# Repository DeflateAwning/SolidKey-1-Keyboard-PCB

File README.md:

# SolidKey-1-Keyboard-PCB
A capacitive touch QMK keyboard, with aspirations of replacing the Framework 13 keyboard

## Inspiration

* This project is inspired by [ebastler's UnMechanical Keyboard](https://github.com/ebastler/UnMechanical).

## Goals

* Make a columnar keyboard with a capacitive touch interface.
* Make the keyboard fit between the Framework 13 keyboard space and screen. Be compatible with the Framework 13 input cover's wiring.
* Base the locations of the keys on the Iris 6 keyboard.
* Parts:
    * RP2040 microcontroller
    * USB-C
    * Vibration motor
    * No LEDs!
* Low-ish power, low mass
* <$80 for a fully-assembled keyboard from JLCPCB

## Licence

The hardware component of this project is licenced under the `CERN Open Hardware Licence Version 2 - Weakly Reciprocal` licence. Variations must be shared under the same licence (or equivalent) licence. Commercial use is allowed, but the source must be shared, and it must be released/sold under a different name.

## Notes

* Framework 13 keyboard dimensions: 276.76mm x 105.0mm x 1.74mm, at the bottom of the taper up, based on their full STEP CAD model.
* For the 276mm x 105mm PCB from JLCPCB, it costs:
    * US$16.80 for 0.6mm thick, LeadFree HASL
    * US$60.60 for 0.4mm thick, requiring ENIG
    * US$10 shipping for these thin boards.
    * US$50 for 0.6mm assembly ("Standard"), but US$26 for 0.8mm assembly ("Economic").
    * 0.8mm weighs 54g each. 0.6mm weighs 40g-54g each.

## Resources

* RP2040 Design Guide: https://datasheets.raspberrypi.com/rp2040/hardware-design-with-rp2040.pdf
* CY8CMBR3116 Capacitive Touch Guides:
    * Datasheet: https://www.infineon.com/cms/en/product/microcontroller/sensing-controller/capsense-controllers/capsense-mbr3/cy8cmbr3116-lqxit/
    * CY8CMBR3xxx CapSense Design Guide: https://www.cypress.com/?rID=90800
    * Getting Started with CapSense: https://www.cypress.com/?rID=48787

## Future Work

* Add a dot mouse thing, like the ThinkPad keyboards.

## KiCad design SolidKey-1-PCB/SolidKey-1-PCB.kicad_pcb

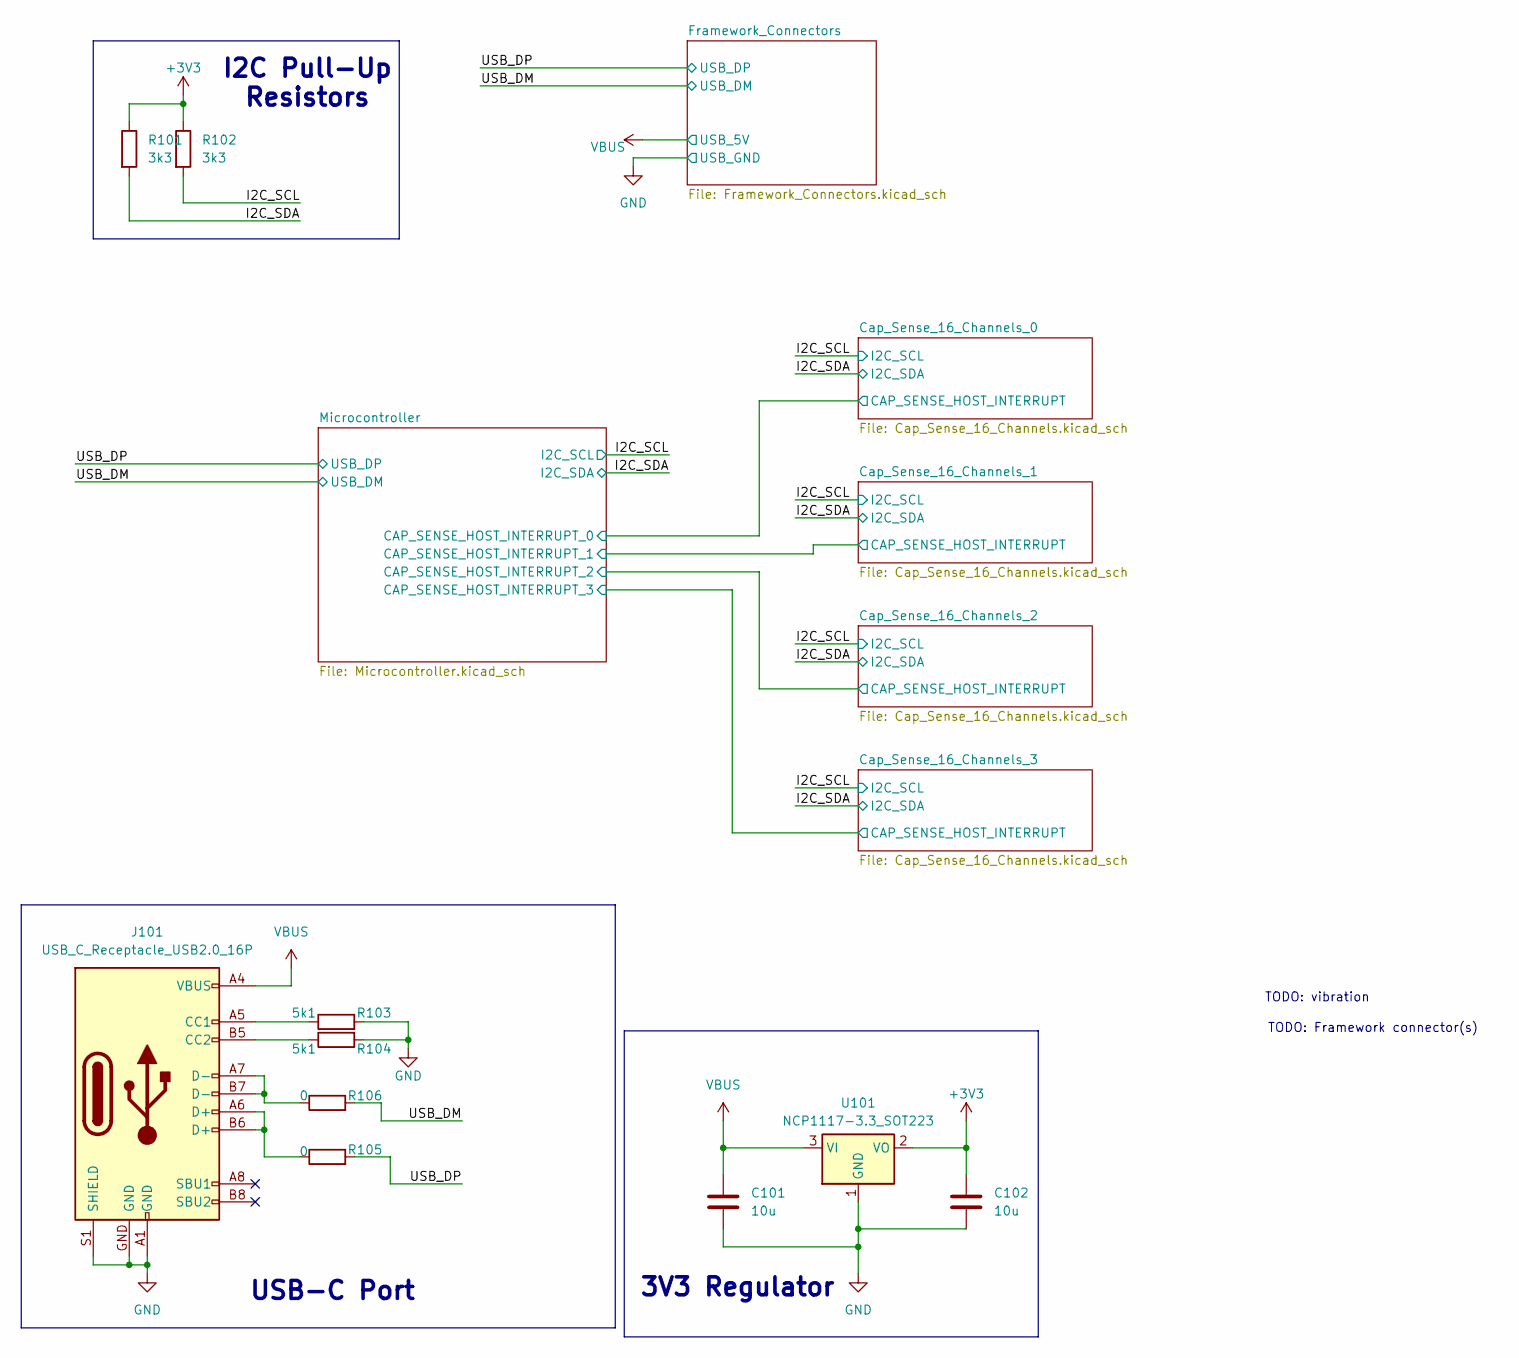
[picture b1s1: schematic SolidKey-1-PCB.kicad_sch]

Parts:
C101, C102: 10u; C_0402_1005Metric
J101: USB_C_Receptacle_USB2.0_16P; USB_C_Receptacle_G-Switch_GT-USB-7025
R101, R102: 3k3; R_0402_1005Metric
R103, R104: 5k1; R_0402_1005Metric
R105, R106: 0; R_0603_1608Metric
U101: NCP1117-3.3_SOT223; SOT-223-3_TabPin2

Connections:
+3V3: C102.1, R101.1, R102.1, U101.2 (VO); also elsewhere on the board
/I2C_SCL: R102.2; also elsewhere on the board
/I2C_SDA: R101.2; also elsewhere on the board
/USB_DM: R106.2; also elsewhere on the board
/USB_DP: R105.2; also elsewhere on the board
GND: C101.2, C102.2, J101.A1 (GND), J101.A12 (GND), J101.B1 (GND), J101.B12 (GND), J101.GND, J101.S1 (SHIELD), R103.2, R104.2, U101.1 (GND); also elsewhere on the board
unnamed: J101.A5 (CC1), R103.1
unnamed: J101.B5 (CC2), R104.1
unnamed: J101.A6 (D+), J101.B6 (D+), R105.1
unnamed: J101.A7 (D-), J101.B7 (D-), R106.1
VBUS: C101.1, J101.A4 (VBUS), J101.A9 (VBUS), J101.B4 (VBUS), J101.B9 (VBUS), U101.3 (VI); also elsewhere on the board

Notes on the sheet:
3V3 Regulator
I2C Pull-Up Resistors
TODO: Framework connector(s)
USB-C Port
TODO: vibration

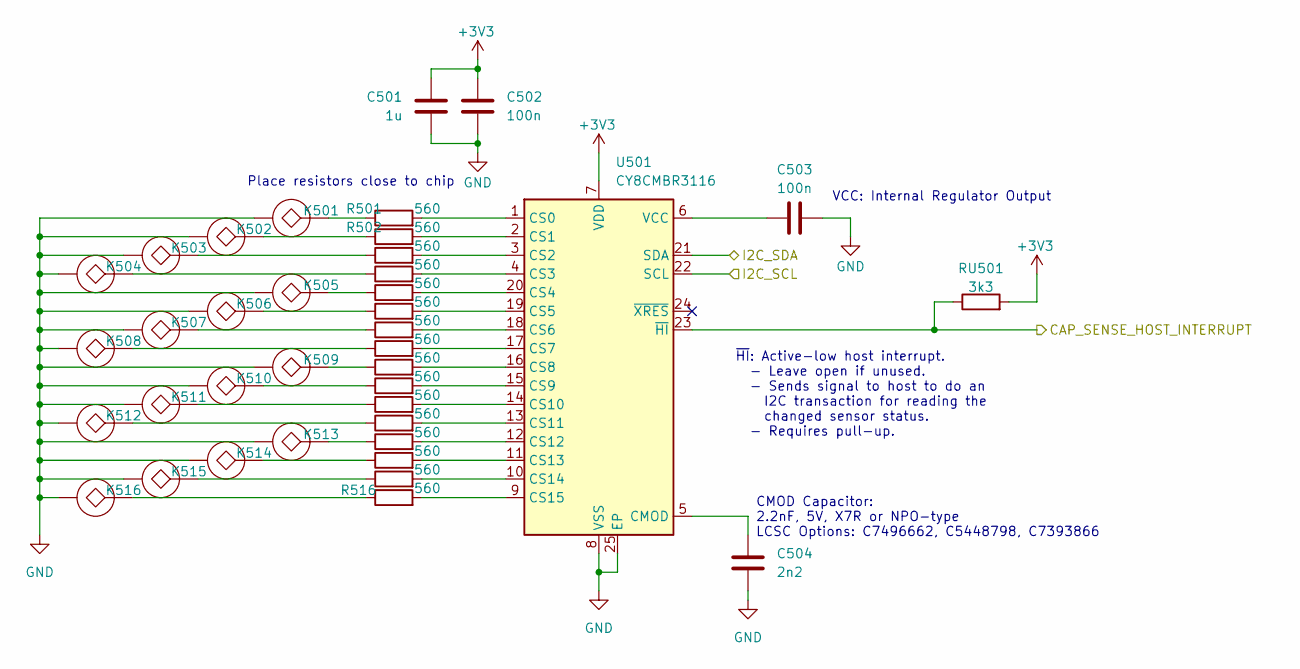
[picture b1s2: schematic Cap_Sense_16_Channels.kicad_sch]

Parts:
C501: 1u; C_0402_1005Metric
C502, C503: 100n; C_0402_1005Metric
C504: 2n2; C_0402_1005Metric; LCSC C7393866
K501, K502, K503, K504, K505, K506, K507, K508, K510, K511, K512, K514, K515, K516: TouchPoint; KeySwitch1_General
K509, K513: TouchPoint; KeySwitch1_Index
R501, R502, R503, R504, R505, R506, R507, R508, R509, R510, R511, R512, R513, R514, R515, R516: 560; R_0603_1608Metric
RU501: 3k3; R_0402_1005Metric
U501: CY8CMBR3116; QFN-24-1EP_4x4mm_P0.5mm_EP2.6x2.6mm

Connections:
+3V3: C501.1, C502.1, RU501.2, U501.7 (VDD); also elsewhere on the board
/Cap_Sense_16_Channels_2/CAP_SENSE_HOST_INTERRUPT: RU501.1, U501.23 (~HI); also elsewhere on the board
/I2C_SCL: U501.22 (SCL); also elsewhere on the board
/I2C_SDA: U501.21 (SDA); also elsewhere on the board
GND: C501.2, C502.2, C503.2, C504.2, K501.2 (GND), K502.2 (GND), K503.2 (GND), K504.2 (GND), K505.2 (GND), K506.2 (GND), K507.2 (GND), K508.2 (GND), K509.2 (GND), K510.2 (GND), K511.2 (GND), K512.2 (GND), K513.2 (GND), K514.2 (GND), K515.2 (GND), K516.2 (GND), U501.8 (VSS), U501.25 (EP); also elsewhere on the board
unnamed: K501.1, R501.1
unnamed: K502.1, R502.1
unnamed: K503.1, R503.1
unnamed: K504.1, R504.1
unnamed: K505.1, R505.1
unnamed: K506.1, R506.1
unnamed: K507.1, R507.1
unnamed: K508.1, R508.1
unnamed: K509.1, R509.1
unnamed: K510.1, R510.1
unnamed: K511.1, R511.1
unnamed: K512.1, R512.1
unnamed: K513.1, R513.1
unnamed: K514.1, R514.1
unnamed: K515.1, R515.1
unnamed: K516.1, R516.1
unnamed: C504.1, U501.5 (CMOD)
unnamed: R501.2, U501.1 (CS0)
unnamed: R502.2, U501.2 (CS1)
unnamed: R503.2, U501.3 (CS2)
unnamed: R504.2, U501.4 (CS3)
unnamed: R505.2, U501.20 (CS4)
unnamed: R506.2, U501.19 (CS5)
unnamed: R507.2, U501.18 (CS6)
unnamed: R508.2, U501.17 (CS7)
unnamed: R509.2, U501.16 (CS8)
unnamed: R510.2, U501.15 (CS9)
unnamed: R511.2, U501.14 (CS10)
unnamed: R512.2, U501.13 (CS11)
unnamed: R513.2, U501.12 (CS12)
unnamed: R514.2, U501.11 (CS13)
unnamed: R515.2, U501.10 (CS14)
unnamed: R516.2, U501.9 (CS15)
unnamed: C503.1, U501.6 (VCC)

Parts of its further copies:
C301, C401, C601: 1u; C_0402_1005Metric
C302, C303, C402, C403, C602, C603: 100n; C_0402_1005Metric
C304, C404, C604: 2n2; C_0402_1005Metric; LCSC C7393866
K301, K302, K303, K304, K305, K306, K307, K308, K310, K311, K312, K314, K315, K316, K401, K402, K403, K404, K405, K406, K407, K408, K410, K411, K412, K414, K415, K416, K601, K602, K603, K604, K605, K606, K607, K608, K610, K611, K612, K614, K615, K616: TouchPoint; KeySwitch1_General
K309, K313, K409, K413, K609, K613: TouchPoint; KeySwitch1_Index
R301, R302, R303, R304, R305, R306, R307, R308, R309, R310, R311, R312, R313, R314, R315, R316, R401, R402, R403, R404, R405, R406, R407, R408, R409, R410, R411, R412, R413, R414, R415, R416, R601, R602, R603, R604, R605, R606, R607, R608, R609, R610, R611, R612, R613, R614, R615, R616: 560; R_0603_1608Metric
RU301, RU401, RU601: 3k3; R_0402_1005Metric
U301, U401, U601: CY8CMBR3116; QFN-24-1EP_4x4mm_P0.5mm_EP2.6x2.6mm

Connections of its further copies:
+3V3: C301.1, C302.1, C401.1, C402.1, C601.1, C602.1, RU301.2, RU401.2, RU601.2, U301.7 (VDD), U401.7 (VDD), U601.7 (VDD); also elsewhere on the board
/Cap_Sense_16_Channels_0/CAP_SENSE_HOST_INTERRUPT: RU301.1, U301.23 (~HI); also elsewhere on the board
/Cap_Sense_16_Channels_1/CAP_SENSE_HOST_INTERRUPT: RU401.1, U401.23 (~HI); also elsewhere on the board
/Cap_Sense_16_Channels_3/CAP_SENSE_HOST_INTERRUPT: RU601.1, U601.23 (~HI); also elsewhere on the board
/I2C_SCL: U301.22 (SCL), U401.22 (SCL), U601.22 (SCL); also elsewhere on the board
/I2C_SDA: U301.21 (SDA), U401.21 (SDA), U601.21 (SDA); also elsewhere on the board
GND: C301.2, C302.2, C303.2, C304.2, C401.2, C402.2, C403.2, C404.2, C601.2, C602.2, C603.2, C604.2, K301.2 (GND), K302.2 (GND), K303.2 (GND), K304.2 (GND), K305.2 (GND), K306.2 (GND), K307.2 (GND), K308.2 (GND), K309.2 (GND), K310.2 (GND), K311.2 (GND), K312.2 (GND), K313.2 (GND), K314.2 (GND), K315.2 (GND), K316.2 (GND), K401.2 (GND), K402.2 (GND), K403.2 (GND), K404.2 (GND), K405.2 (GND), K406.2 (GND), K407.2 (GND), K408.2 (GND), K409.2 (GND), K410.2 (GND), K411.2 (GND), K412.2 (GND), K413.2 (GND), K414.2 (GND), K415.2 (GND), K416.2 (GND), K601.2 (GND), K602.2 (GND), K603.2 (GND), K604.2 (GND), K605.2 (GND), K606.2 (GND), K607.2 (GND), K608.2 (GND), K609.2 (GND), K610.2 (GND), K611.2 (GND), K612.2 (GND), K613.2 (GND), K614.2 (GND), K615.2 (GND), K616.2 (GND), U301.8 (VSS), U301.25 (EP), U401.8 (VSS), U401.25 (EP), U601.8 (VSS), U601.25 (EP); also elsewhere on the board
unnamed: K301.1, R301.1
unnamed: K302.1, R302.1
unnamed: K303.1, R303.1
unnamed: K304.1, R304.1
unnamed: K305.1, R305.1
unnamed: K306.1, R306.1
unnamed: K307.1, R307.1
unnamed: K308.1, R308.1
unnamed: K309.1, R309.1
unnamed: K310.1, R310.1
unnamed: K311.1, R311.1
unnamed: K312.1, R312.1
unnamed: K313.1, R313.1
unnamed: K314.1, R314.1
unnamed: K315.1, R315.1
unnamed: K316.1, R316.1
unnamed: K401.1, R401.1
unnamed: K402.1, R402.1
unnamed: K403.1, R403.1
unnamed: K404.1, R404.1
unnamed: K405.1, R405.1
unnamed: K406.1, R406.1
unnamed: K407.1, R407.1
unnamed: K408.1, R408.1
unnamed: K409.1, R409.1
unnamed: K410.1, R410.1
unnamed: K411.1, R411.1
unnamed: K412.1, R412.1
unnamed: K413.1, R413.1
unnamed: K414.1, R414.1
unnamed: K415.1, R415.1
unnamed: K416.1, R416.1
unnamed: K601.1, R601.1
unnamed: K602.1, R602.1
unnamed: K603.1, R603.1
unnamed: K604.1, R604.1
unnamed: K605.1, R605.1
unnamed: K606.1, R606.1
unnamed: K607.1, R607.1
unnamed: K608.1, R608.1
unnamed: K609.1, R609.1
unnamed: K610.1, R610.1
unnamed: K611.1, R611.1
unnamed: K612.1, R612.1
unnamed: K613.1, R613.1
unnamed: K614.1, R614.1
unnamed: K615.1, R615.1
unnamed: K616.1, R616.1
unnamed: C304.1, U301.5 (CMOD)
unnamed: R301.2, U301.1 (CS0)
unnamed: R302.2, U301.2 (CS1)
unnamed: R303.2, U301.3 (CS2)
unnamed: R304.2, U301.4 (CS3)
unnamed: R305.2, U301.20 (CS4)
unnamed: R306.2, U301.19 (CS5)
unnamed: R307.2, U301.18 (CS6)
unnamed: R308.2, U301.17 (CS7)
unnamed: R309.2, U301.16 (CS8)
unnamed: R310.2, U301.15 (CS9)
unnamed: R311.2, U301.14 (CS10)
unnamed: R312.2, U301.13 (CS11)
unnamed: R313.2, U301.12 (CS12)
unnamed: R314.2, U301.11 (CS13)
unnamed: R315.2, U301.10 (CS14)
unnamed: R316.2, U301.9 (CS15)
unnamed: C303.1, U301.6 (VCC)
unnamed: C404.1, U401.5 (CMOD)
unnamed: R401.2, U401.1 (CS0)
unnamed: R402.2, U401.2 (CS1)
unnamed: R403.2, U401.3 (CS2)
unnamed: R404.2, U401.4 (CS3)
unnamed: R405.2, U401.20 (CS4)
unnamed: R406.2, U401.19 (CS5)
unnamed: R407.2, U401.18 (CS6)
unnamed: R408.2, U401.17 (CS7)
unnamed: R409.2, U401.16 (CS8)
unnamed: R410.2, U401.15 (CS9)
unnamed: R411.2, U401.14 (CS10)
unnamed: R412.2, U401.13 (CS11)
unnamed: R413.2, U401.12 (CS12)
unnamed: R414.2, U401.11 (CS13)
unnamed: R415.2, U401.10 (CS14)
unnamed: R416.2, U401.9 (CS15)
unnamed: C403.1, U401.6 (VCC)
unnamed: C604.1, U601.5 (CMOD)
unnamed: R601.2, U601.1 (CS0)
unnamed: R602.2, U601.2 (CS1)
unnamed: R603.2, U601.3 (CS2)
unnamed: R604.2, U601.4 (CS3)
unnamed: R605.2, U601.20 (CS4)
unnamed: R606.2, U601.19 (CS5)
unnamed: R607.2, U601.18 (CS6)
unnamed: R608.2, U601.17 (CS7)
unnamed: R609.2, U601.16 (CS8)
unnamed: R610.2, U601.15 (CS9)
unnamed: R611.2, U601.14 (CS10)
unnamed: R612.2, U601.13 (CS11)
unnamed: R613.2, U601.12 (CS12)
unnamed: R614.2, U601.11 (CS13)
unnamed: R615.2, U601.10 (CS14)
unnamed: R616.2, U601.9 (CS15)
unnamed: C603.1, U601.6 (VCC)

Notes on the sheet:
CMOD Capacitor: 2.2nF, 5V, X7R or NPO-type LCSC Options: C7496662, C5448798, C7393866
~{HI}: Active-low host interrupt. - Leave open if unused. - Sends signal to host to do an I2C transaction for reading the changed sensor status. - Requires pull-up.
Place resistors close to chip
VCC: Internal Regulator Output

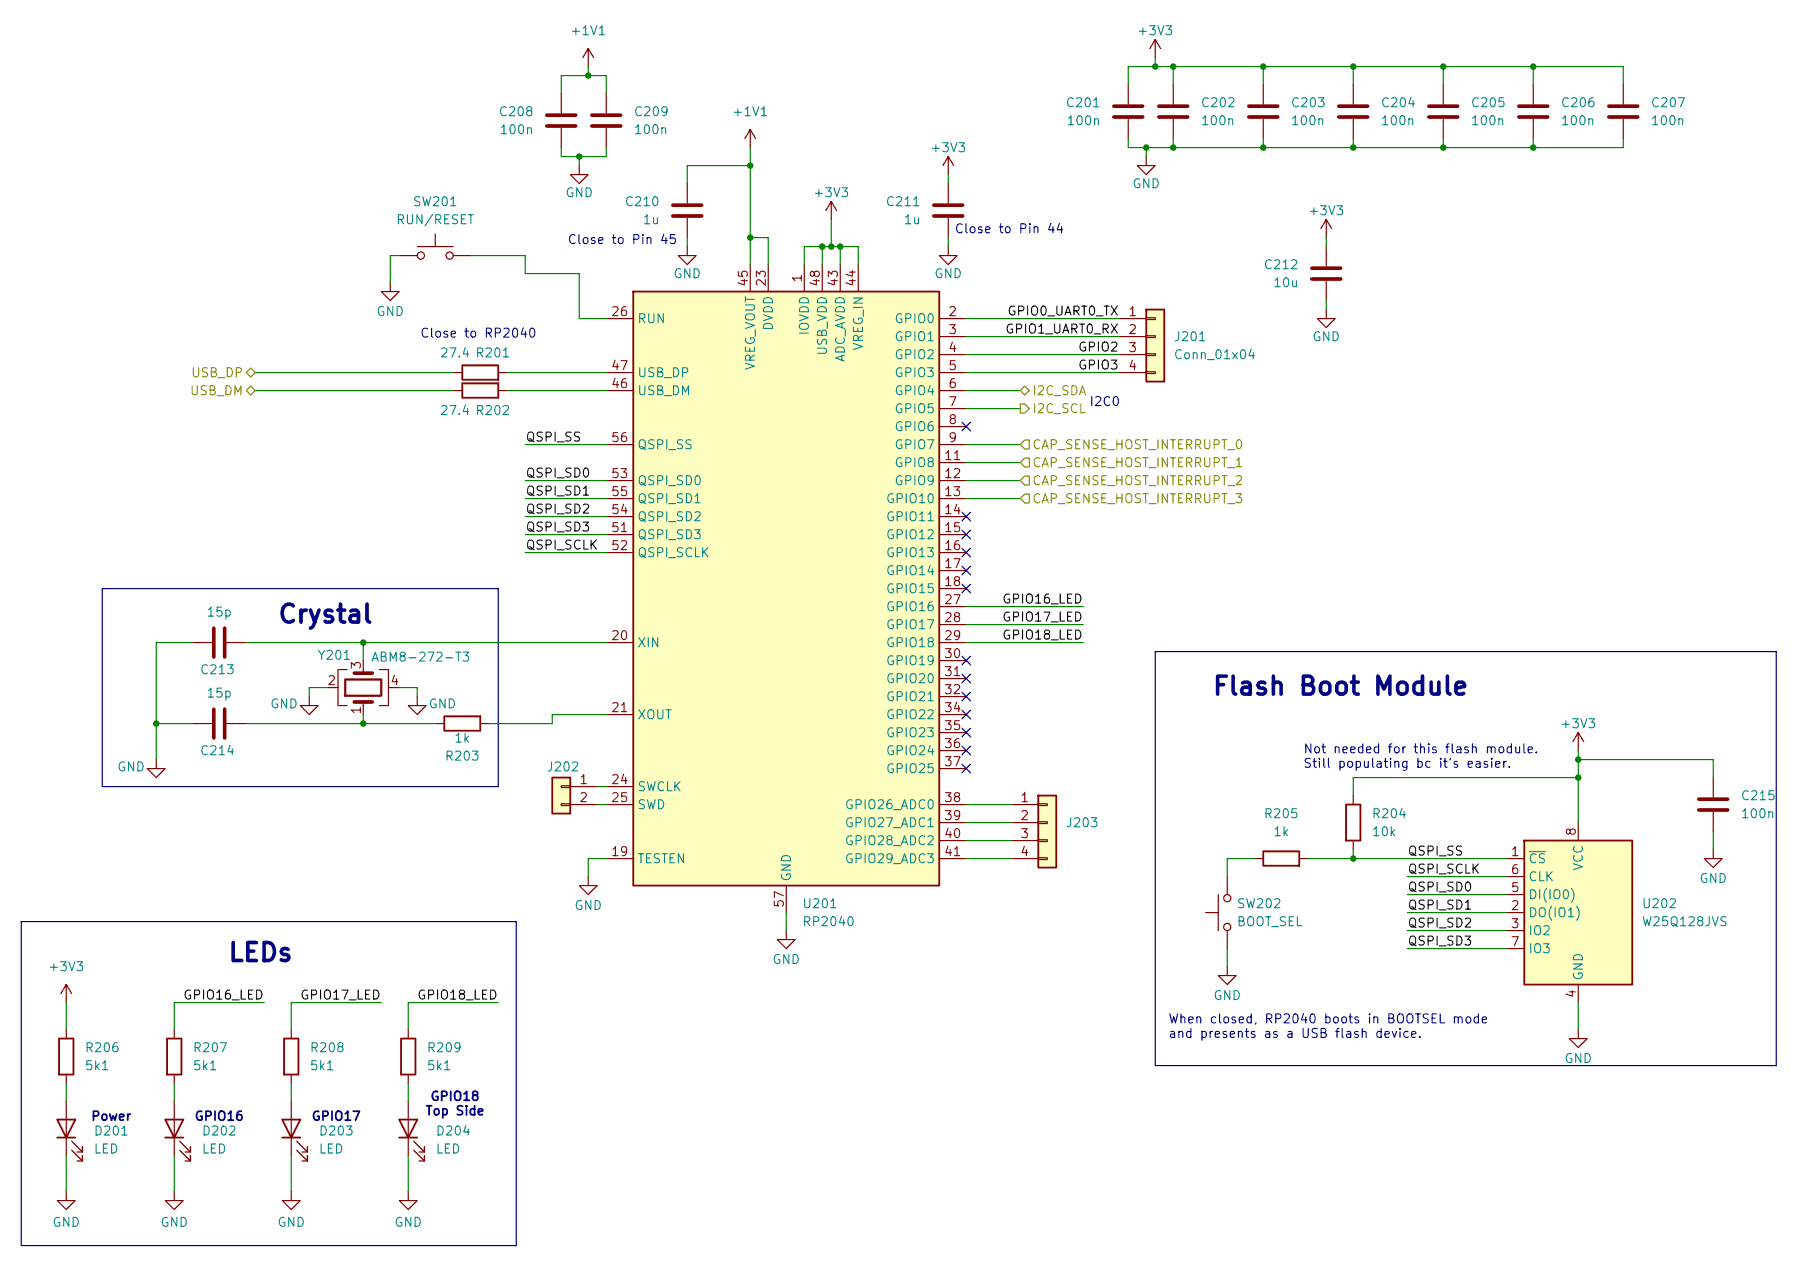
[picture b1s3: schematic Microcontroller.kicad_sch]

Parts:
C201, C202, C203, C204, C205, C206, C207, C208, C209, C215: 100n; C_0402_1005Metric
C210, C211: 1u; C_0402_1005Metric
C212: 10u; C_0402_1005Metric
C213, C214: 15p; C_0402_1005Metric
D201, D202, D203, D204: LED; LED_0603_1608Metric
J201, J203: Conn_01x04; PinHeader_1x04_P2.54mm_Vertical_SMD_Pin1Left
J202: Conn_01x02; PinHeader_1x02_P2.54mm_Vertical_SMD_Pin1Left
R201, R202: 27.4; R_0402_1005Metric
R203, R205: 1k; R_0402_1005Metric
R204: 10k; R_0402_1005Metric
R206, R207, R208, R209: 5k1; R_0402_1005Metric
SW201: RUN/RESET; SW_Push_1P1T_XKB_TS-1187A; LCSC C318884
SW202: BOOT_SEL; SW_Push_1P1T_XKB_TS-1187A; LCSC C318884
U201: RP2040; QFN-56-1EP_7x7mm_P0.4mm_EP3.2x3.2mm
U202: W25Q128JVS; SOIC-8_5.23x5.23mm_P1.27mm; LCSC C97521
Y201: ABM8-272-T3; Crystal_SMD_3225-4Pin_3.2x2.5mm; LCSC C20625731

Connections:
+1V1: C208.1, C209.1, C210.1, U201.23 (DVDD), U201.45 (VREG_VOUT), U201.50 (DVDD)
+3V3: C201.1, C202.1, C203.1, C204.1, C205.1, C206.1, C207.1, C211.1, C212.1, C215.1, R204.1, R206.1, U201.1 (IOVDD), U201.10 (IOVDD), U201.22 (IOVDD), U201.33 (IOVDD), U201.42 (IOVDD), U201.43 (ADC_AVDD), U201.44 (VREG_IN), U201.48 (USB_VDD), U201.49 (IOVDD), U202.8 (VCC); also elsewhere on the board
/Cap_Sense_16_Channels_0/CAP_SENSE_HOST_INTERRUPT: U201.9 (GPIO7); also elsewhere on the board
/Cap_Sense_16_Channels_1/CAP_SENSE_HOST_INTERRUPT: U201.11 (GPIO8); also elsewhere on the board
/Cap_Sense_16_Channels_2/CAP_SENSE_HOST_INTERRUPT: U201.12 (GPIO9); also elsewhere on the board
/Cap_Sense_16_Channels_3/CAP_SENSE_HOST_INTERRUPT: U201.13 (GPIO10); also elsewhere on the board
/I2C_SCL: U201.7 (GPIO5); also elsewhere on the board
/I2C_SDA: U201.6 (GPIO4); also elsewhere on the board
/Microcontroller/GPIO0_UART0_TX: J201.1, U201.2 (GPIO0)
/Microcontroller/GPIO1_UART0_RX: J201.2, U201.3 (GPIO1)
/Microcontroller/GPIO2: J201.3, U201.4 (GPIO2)
/Microcontroller/GPIO3: J201.4, U201.5 (GPIO3)
/Microcontroller/GPIO16_LED: R207.1, U201.27 (GPIO16)
/Microcontroller/GPIO17_LED: R208.1, U201.28 (GPIO17)
/Microcontroller/GPIO18_LED: R209.1, U201.29 (GPIO18)
/Microcontroller/QSPI_SCLK: U201.52 (QSPI_SCLK), U202.6 (CLK)
/Microcontroller/QSPI_SD0: U201.53 (QSPI_SD0), U202.5 (DI(IO0))
/Microcontroller/QSPI_SD1: U201.55 (QSPI_SD1), U202.2 (DO(IO1))
/Microcontroller/QSPI_SD2: U201.54 (QSPI_SD2), U202.3 (IO2)
/Microcontroller/QSPI_SD3: U201.51 (QSPI_SD3), U202.7 (IO3)
/Microcontroller/QSPI_SS: R204.2, R205.2, U201.56 (QSPI_SS), U202.1 (~CS)
/USB_DM: R202.1; also elsewhere on the board
/USB_DP: R201.1; also elsewhere on the board
GND: C201.2, C202.2, C203.2, C204.2, C205.2, C206.2, C207.2, C208.2, C209.2, C210.2, C211.2, C212.2, C213.1, C214.1, C215.2, D201.1 (K), D202.1 (K), D203.1 (K), D204.1 (K), SW201.1, SW202.1, U201.19 (TESTEN), U201.57 (GND), U202.4 (GND), Y201.2, Y201.4; also elsewhere on the board
unnamed: C214.2, R203.1, Y201.1
unnamed: D201.2 (A), R206.2
unnamed: D202.2 (A), R207.2
unnamed: D203.2 (A), R208.2
unnamed: D204.2 (A), R209.2
unnamed: J202.1, U201.24 (SWCLK)
unnamed: J202.2, U201.25 (SWD)
unnamed: J203.1, U201.38 (GPIO26_ADC0)
unnamed: J203.2, U201.39 (GPIO27_ADC1)
unnamed: J203.3, U201.40 (GPIO28_ADC2)
unnamed: J203.4, U201.41 (GPIO29_ADC3)
unnamed: R205.1, SW202.2
unnamed: SW201.2, U201.26 (RUN)
unnamed: R202.2, U201.46 (USB_DM)
unnamed: R201.2, U201.47 (USB_DP)
unnamed: C213.2, U201.20 (XIN), Y201.3
unnamed: R203.2, U201.21 (XOUT)

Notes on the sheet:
GPIO16
When closed, RP2040 boots in BOOTSEL mode and presents as a USB flash device.
Close to RP2040
GPIO17
Flash Boot Module
Power
LEDs
Not needed for this flash module. Still populating bc it's easier.
GPIO18 Top Side
Crystal
Close to Pin 45
I2C0
Close to Pin 44

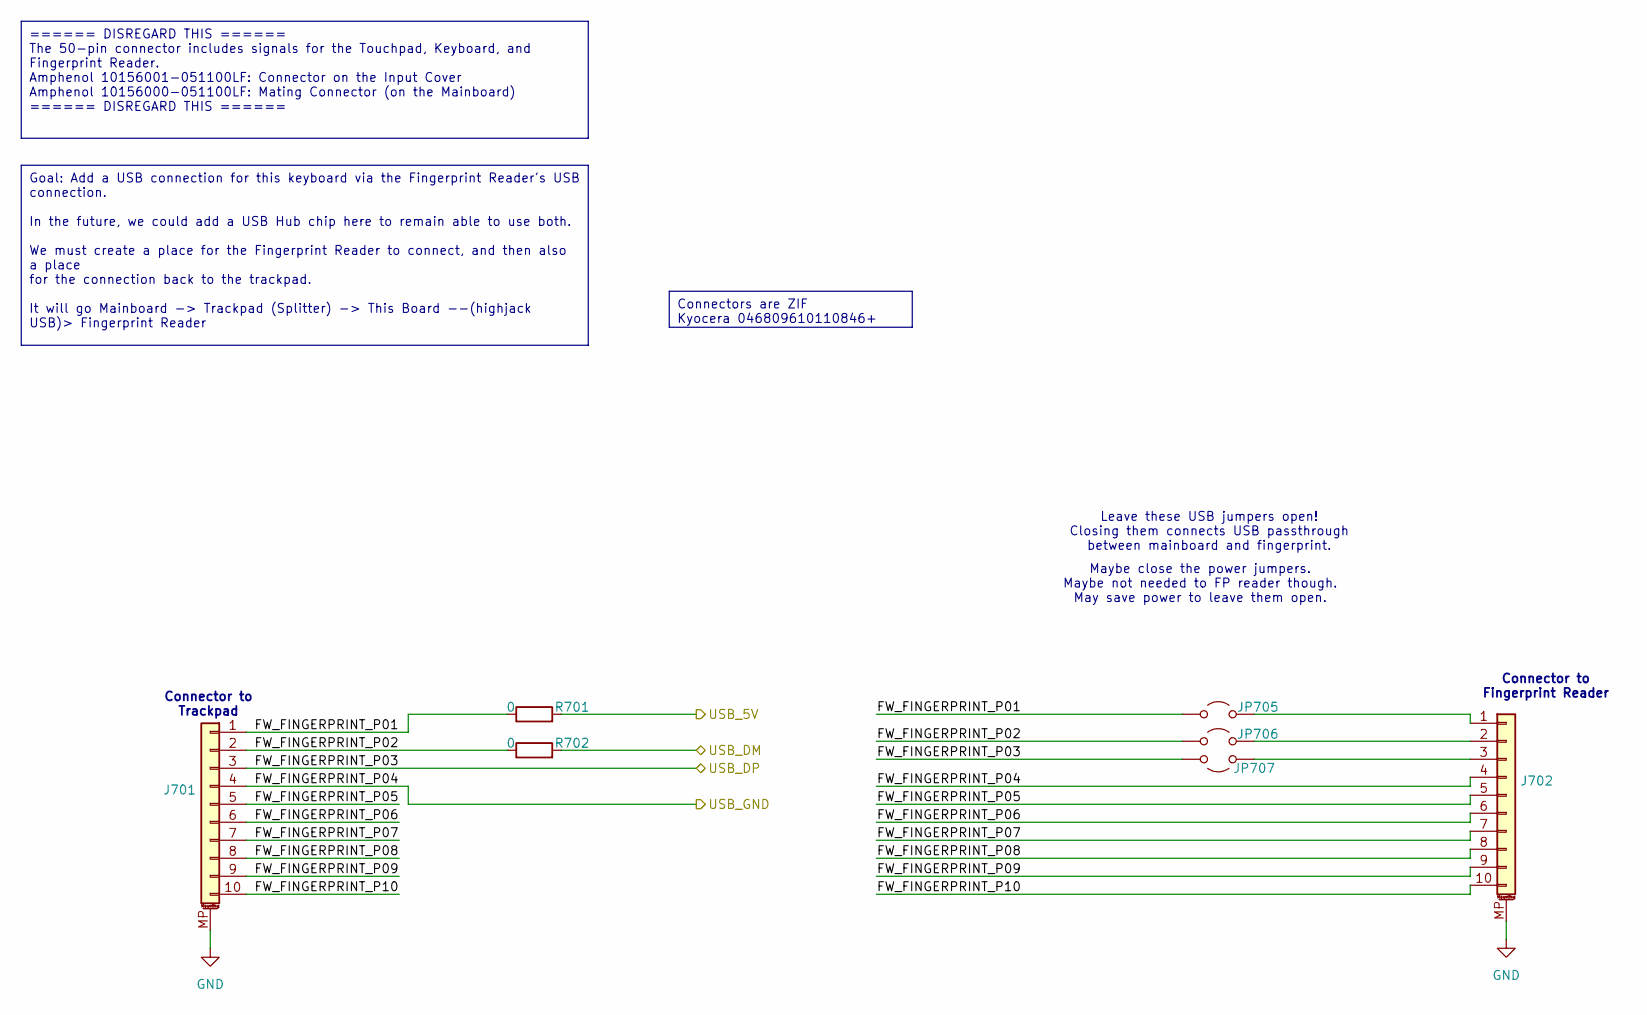
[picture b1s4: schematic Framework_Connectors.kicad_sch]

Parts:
J701, J702: Conn_01x10_MountingPin; 046809610110846
JP705, JP706, JP707: Jumper_2_Open; SolderJumper-2_P1.3mm_Open_XSilk_RoundedPad1.0x1.5mm
R701, R702: 0; R_0603_1608Metric

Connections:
/Framework_Connectors/FW_FINGERPRINT_P01: J701.1, JP705.2 (B), R701.1
/Framework_Connectors/FW_FINGERPRINT_P02: J701.2, JP706.2 (B), R702.1
/Framework_Connectors/FW_FINGERPRINT_P05: J701.5, J702.5
/Framework_Connectors/FW_FINGERPRINT_P06: J701.6, J702.6
/Framework_Connectors/FW_FINGERPRINT_P07: J701.7, J702.7
/Framework_Connectors/FW_FINGERPRINT_P08: J701.8, J702.8
/Framework_Connectors/FW_FINGERPRINT_P09: J701.9, J702.9
/Framework_Connectors/FW_FINGERPRINT_P10: J701.10, J702.10
/USB_DM: R702.2; also elsewhere on the board
/USB_DP: J701.3, JP707.2 (B); also elsewhere on the board
GND: J701.4, J701.MP (MountPin), J702.4, J702.MP (MountPin); also elsewhere on the board
unnamed: J702.1, JP705.1 (A)
unnamed: J702.2, JP706.1 (A)
unnamed: J702.3, JP707.1 (A)
VBUS: R701.2; also elsewhere on the board

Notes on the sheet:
Goal: Add a USB connection for this keyboard via the Fingerprint Reader's USB connection. In the future, we could add a USB Hub chip here to remain able to use both. We must create a place for the Fingerprint Reader to connect, and then also a place for the connection back to the trackpad. It will 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
====== DISREGARD THIS ====== The 50-pin connector includes signals for the Touchpad, Keyboard, and Fingerprint Reader. Amphenol 10156001-051100LF: Connector on the Input Cover Amphenol 10156000-051100LF: Mating Connector (on the Mainboard) ====== DISREGARD THIS ======
Connectors are ZIF Kyocera 046809610110846+
Maybe close the power jumpers. Maybe not needed to FP reader though. May save power to leave them open.
Leave these USB jumpers open! Closing them connects USB passthrough between mainboard and fingerprint.
Connector to Trackpad
Connector to Fingerprint Reader

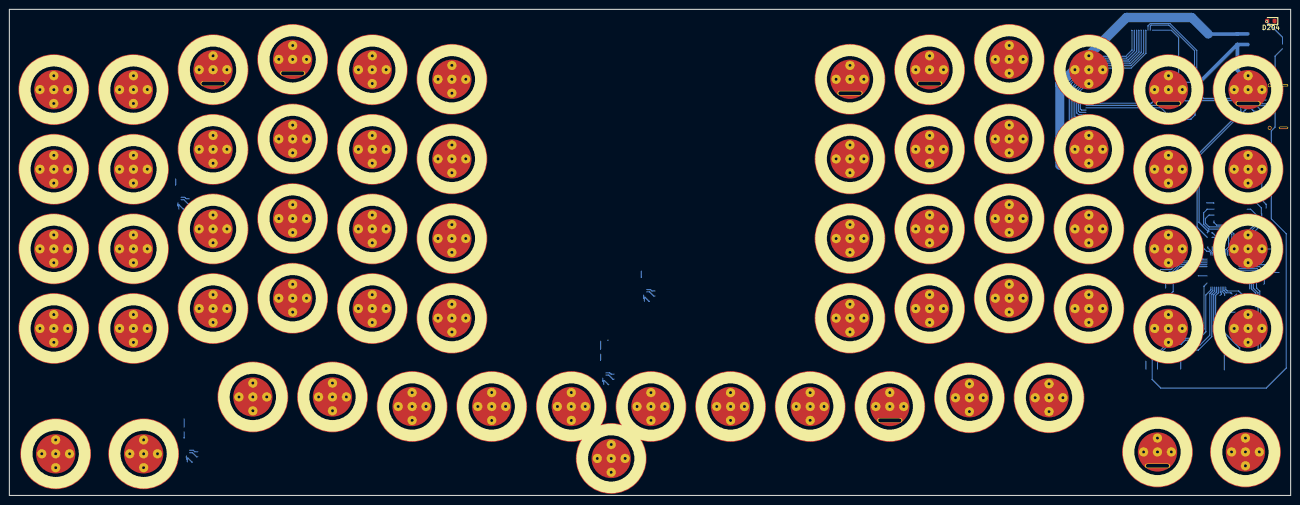
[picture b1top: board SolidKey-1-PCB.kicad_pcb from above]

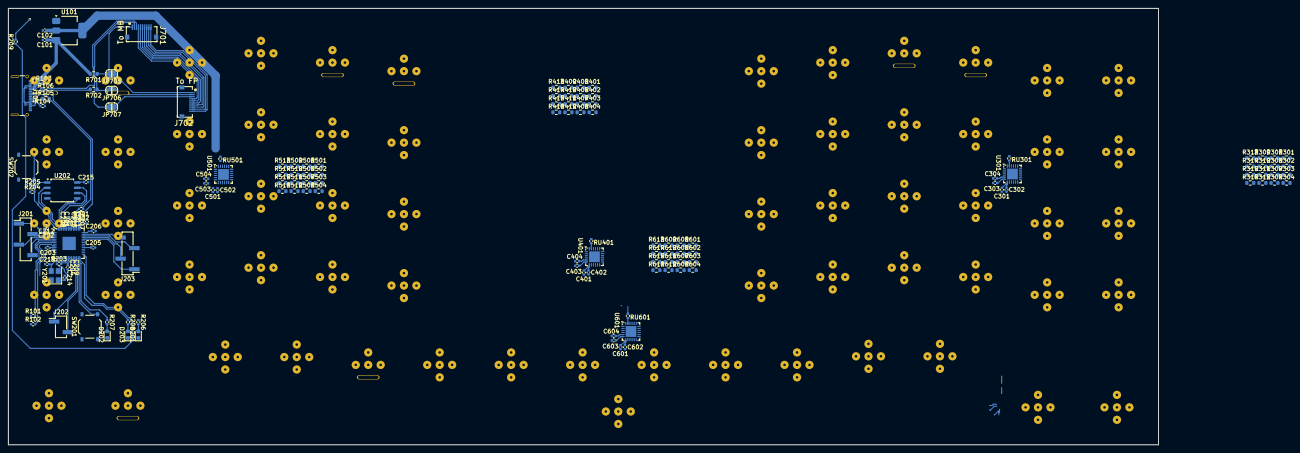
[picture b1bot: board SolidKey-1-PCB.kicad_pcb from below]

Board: 2 copper layers, 276.8 x 105.0 mm, 205 parts (140 on the bottom side), 193 nets.

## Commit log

2024-08-17 Fix gitignore
2024-08-18 Create license
2024-08-18 Outline the project in the README
2024-08-18 Design the keyboard, mostly
2024-08-18 Add Framwork connectors and start routing
2024-08-18 Place each capacitive sensor chip block
2024-08-19 Create Python script to generate key placement definitions
2024-08-19 Attempt rotation parsing
2024-08-19 Finish up key map
2024-08-19 Import final iris layout to PCB
2024-08-19 Prepare to place the keys
2024-08-19 Finish key layout placement
2024-08-19 Reposition CapSense chips
